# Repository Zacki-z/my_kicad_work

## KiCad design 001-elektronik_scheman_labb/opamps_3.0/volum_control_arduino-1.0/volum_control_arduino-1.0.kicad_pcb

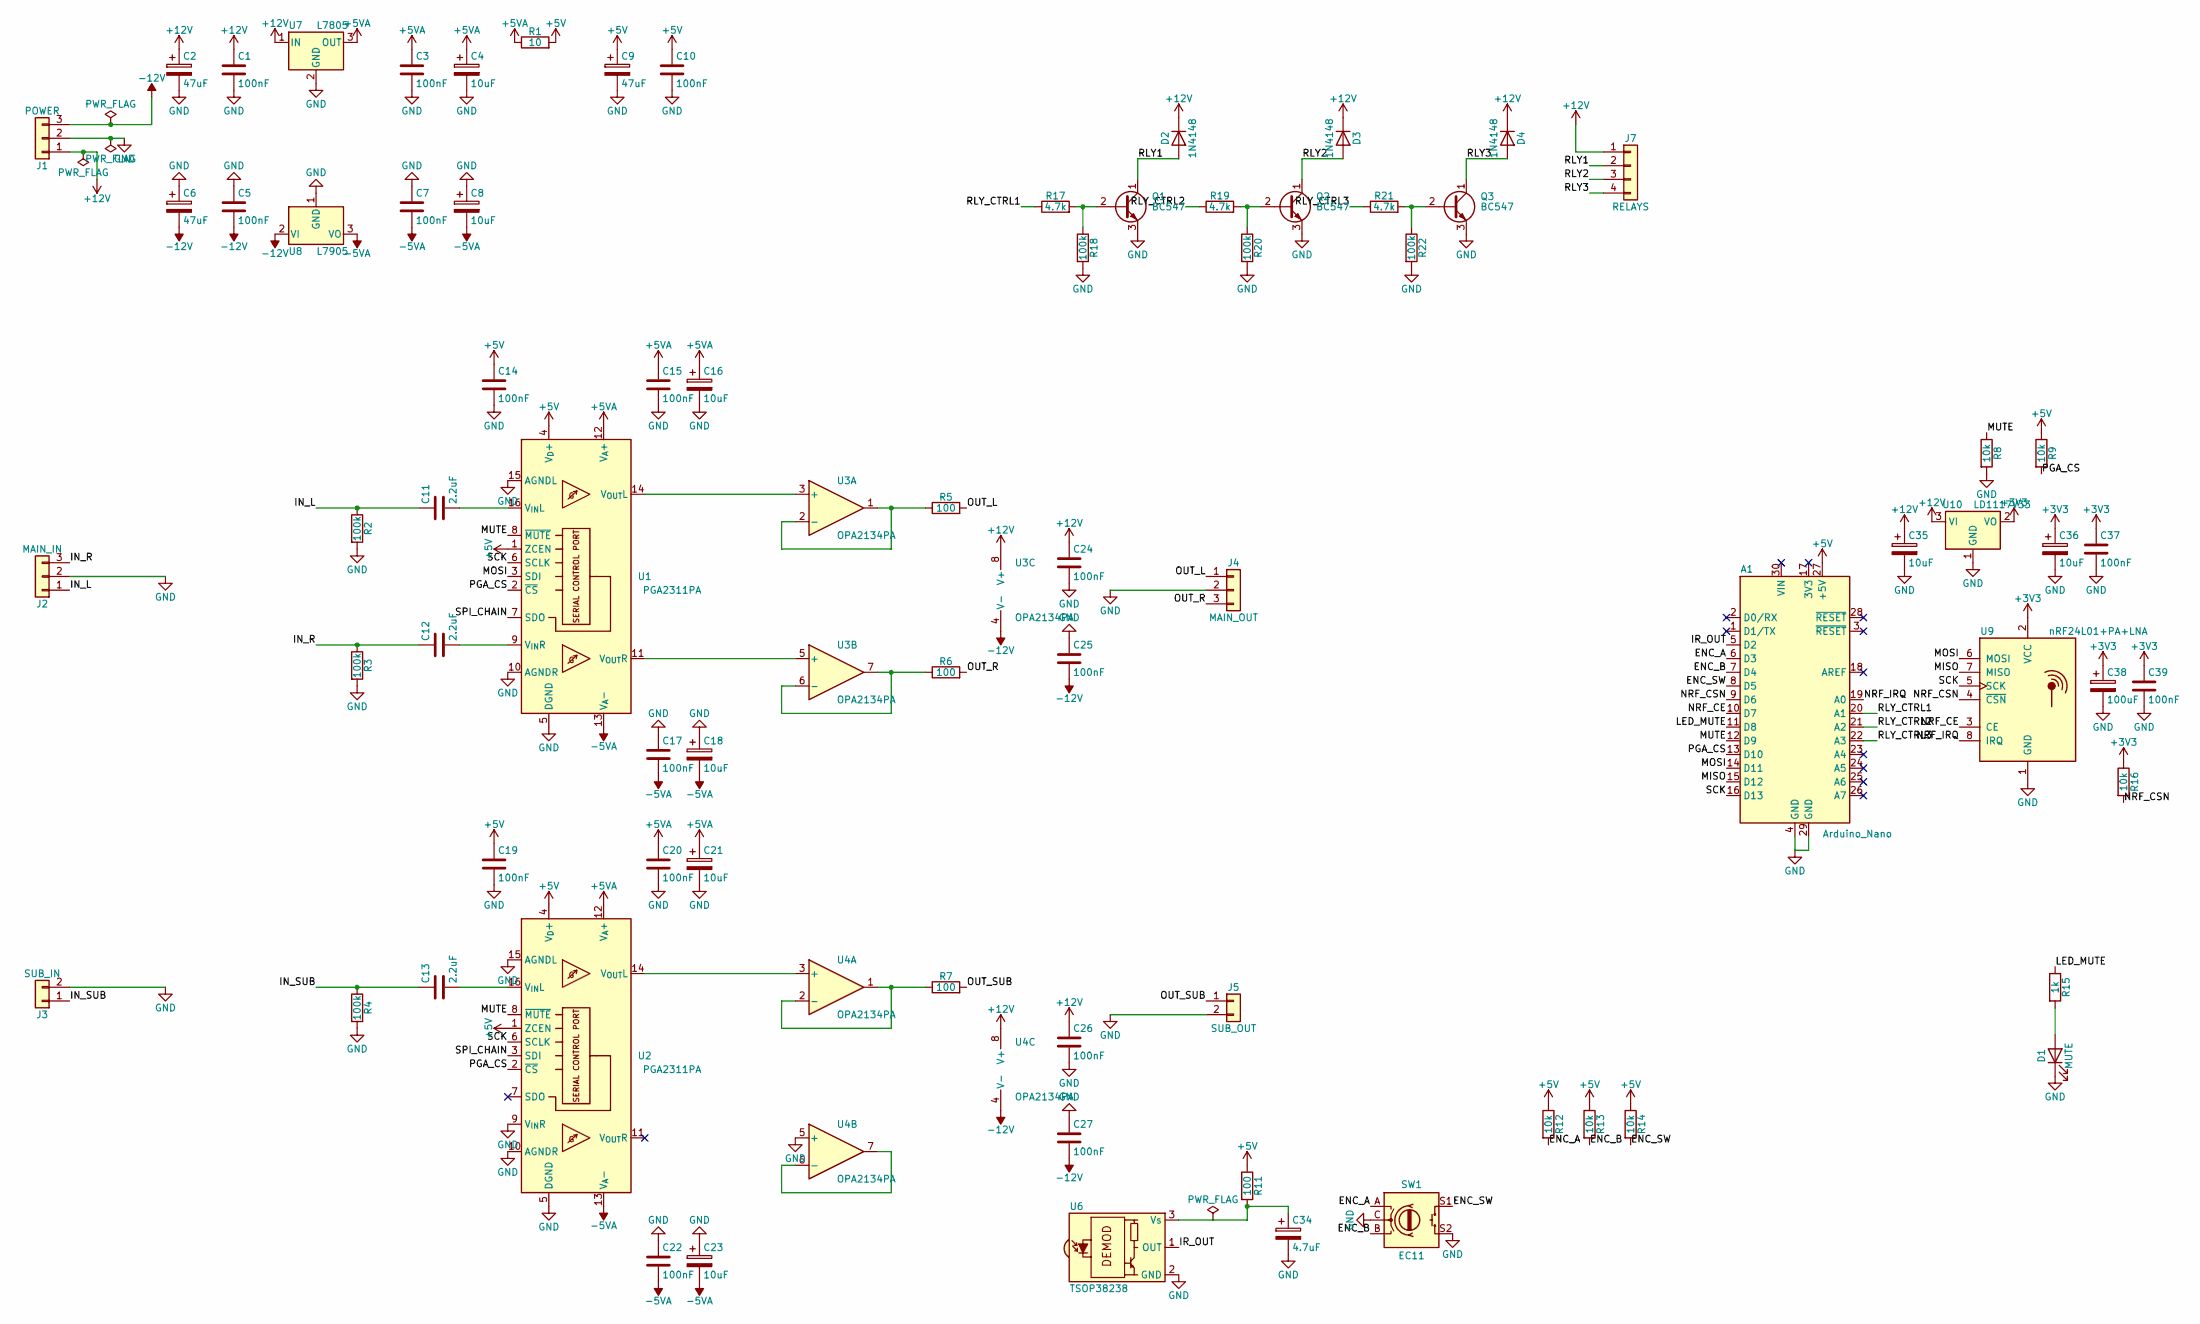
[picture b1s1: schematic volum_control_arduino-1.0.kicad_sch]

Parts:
A1: Arduino_Nano
C1, C3, C5, C7, C10, C14, C15, C17, C19, C20, C22, C24, C25, C26, C27, C37, C39: 100nF; C_Disc_D5.0mm_W2.5mm_P2.50mm
C2, C6, C9: 47uF; CP_Radial_D6.3mm_P2.50mm
C4, C8, C16, C18, C21, C23, C35, C36: 10uF; CP_Radial_D5.0mm_P2.00mm
C11, C12, C13: 2.2uF; C_Rect_L7.2mm_W3.5mm_P5.00mm_FKS2_FKP2_MKS2_MKP2
C34: 4.7uF; CP_Radial_D5.0mm_P2.00mm
C38: 100uF; CP_Radial_D6.3mm_P2.50mm
D1: MUTE; LED_D3.0mm
D2, D3, D4: 1N4148; D_DO-35_SOD27_P7.62mm_Horizontal
J1: POWER; PinHeader_1x03_P2.54mm_Vertical
J2: MAIN_IN; PinHeader_1x03_P2.54mm_Vertical
J3: SUB_IN; PinHeader_1x02_P2.54mm_Vertical
J4: MAIN_OUT; PinHeader_1x03_P2.54mm_Vertical
J5: SUB_OUT; PinHeader_1x02_P2.54mm_Vertical
J7: RELAYS; PinHeader_1x04_P2.54mm_Vertical
Q1, Q2, Q3: BC547; TO-92_Inline
R1: 10; R_Axial_DIN0207_L6.3mm_D2.5mm_P7.62mm_Horizontal
R2, R3, R4, R18, R20, R22: 100k; R_Axial_DIN0207_L6.3mm_D2.5mm_P7.62mm_Horizontal
R5, R6, R7, R11: 100; R_Axial_DIN0207_L6.3mm_D2.5mm_P7.62mm_Horizontal
R8, R9, R12, R13, R14, R16: 10k; R_Axial_DIN0207_L6.3mm_D2.5mm_P7.62mm_Horizontal
R15: 1k; R_Axial_DIN0207_L6.3mm_D2.5mm_P7.62mm_Horizontal
R17, R19, R21: 4.7k; R_Axial_DIN0207_L6.3mm_D2.5mm_P7.62mm_Horizontal
SW1: EC11; RotaryEncoder_Alps_EC11E-Switch_Vertical_H20mm
U1, U2: PGA2311PA; DIP-16_W7.62mm
U3, U4: OPA2134PA; DIP-8_W7.62mm
U6: TSOP38238; Vishay_MINICAST-3Pin
U7: L7805; TO-220-3_Vertical
U8: L7905; TO-220-3_Vertical
U9: nRF24L01+PA+LNA; nRF24L01_Breakout
U10: LD1117V33; TO-220-3_Vertical

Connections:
+3V3: C36.1, C37.1, C38.1, C39.1, R16.1, U9.2 (VCC), U10.2 (VO)
+5V: A1.27 (+5V), C9.1, C10.1, C14.1, C19.1, R1.2, R9.1, R11.1, R12.1, R13.1, R14.1, U1.1 (ZCEN), U1.4 (V_{D}+), U2.1 (ZCEN), U2.4 (V_{D}+)
+5VA: C3.1, C4.1, C15.1, C16.1, C20.1, C21.1, R1.1, U1.12 (V_{A}+), U2.12 (V_{A}+), U7.3 (OUT)
+12V: C1.1, C2.1, C24.1, C26.1, C35.1, D2.1 (K), D3.1 (K), D4.1 (K), J1.1, J7.1, U3.8 (V+), U4.8 (V+), U7.1 (IN), U10.3 (VI)
-5VA: C7.2, C8.2, C17.2, C18.2, C22.2, C23.2, U1.13 (V_{A}-), U2.13 (V_{A}-), U8.3 (VO)
-12V: C5.2, C6.2, C25.2, C27.2, J1.3, U3.4 (V-), U4.4 (V-), U8.2 (VI)
/ENC_A: A1.6 (D3), R12.2, SW1.A
/ENC_B: A1.7 (D4), R13.2, SW1.B
/ENC_SW: A1.8 (D5), R14.2, SW1.S1
/IN_L: C11.1, J2.1, R2.1
/IN_R: C12.1, J2.3, R3.1
/IN_SUB: C13.1, J3.1, R4.1
/IR_OUT: A1.5 (D2), U6.1 (OUT)
/LED_MUTE: A1.11 (D8), R15.1
/MISO: A1.15 (D12), U9.7 (MISO)
/MOSI: A1.14 (D11), U1.3 (SDI), U9.6 (MOSI)
/MUTE: A1.12 (D9), R8.1, U1.8 (~MUTE), U2.8 (~MUTE)
/NRF_CE: A1.10 (D7), U9.3 (CE)
/NRF_CSN: A1.9 (D6), R16.2, U9.4 (~CSN)
/NRF_IRQ: A1.19 (A0), U9.8 (IRQ)
/OUT_L: J4.1, R5.2
/OUT_R: J4.3, R6.2
/OUT_SUB: J5.1, R7.2
/PGA_CS: A1.13 (D10), R9.2, U1.2 (~CS), U2.2 (~CS)
/RLY1: D2.2 (A), J7.2, Q1.1 (C)
/RLY2: D3.2 (A), J7.3, Q2.1 (C)
/RLY3: D4.2 (A), J7.4, Q3.1 (C)
/RLY_CTRL1: A1.20 (A1), R17.1
/RLY_CTRL2: A1.21 (A2), R19.1
/RLY_CTRL3: A1.22 (A3), R21.1
/SCK: A1.16 (D13), U1.6 (SCLK), U2.6 (SCLK), U9.5 (SCK)
/SPI_CHAIN: U1.7 (SDO), U2.3 (SDI)
GND: A1.4 (GND), A1.29 (GND), C1.2, C2.2, C3.2, C4.2, C5.1, C6.1, C7.1, C8.1, C9.2, C10.2, C14.2, C15.2, C16.2, C17.1, C18.1, C19.2, C20.2, C21.2, C22.1, C23.1, C24.2, C25.1, C26.2, C27.1, C34.2, C35.2, C36.2, C37.2, C38.2, C39.2, D1.1 (K), J1.2, J2.2, J3.2, J4.2, J5.2, Q1.3 (E), Q2.3 (E), Q3.3 (E), R2.2, R3.2, R4.2, R8.2, R18.2, R20.2, R22.2, SW1.C, SW1.S2, U1.5 (DGND), U1.10 (AGNDR), U1.15 (AGNDL), U2.5 (DGND), U2.9 (V_{IN}R), U2.10 (AGNDR), U2.15 (AGNDL), U4.5 (+), U6.2 (GND), U7.2 (GND), U8.1 (GND), U9.1 (GND), U10.1 (GND)
unnamed: D1.2 (A), R15.2
unnamed: Q1.2 (B), R17.2, R18.1
unnamed: Q2.2 (B), R19.2, R20.1
unnamed: Q3.2 (B), R21.2, R22.1
unnamed: C11.2, U1.16 (V_{IN}L)
unnamed: C12.2, U1.9 (V_{IN}R)
unnamed: U1.14 (V_{OUT}L), U3.3 (+)
unnamed: U1.11 (V_{OUT}R), U3.5 (+)
unnamed: C13.2, U2.16 (V_{IN}L)
unnamed: U2.14 (V_{OUT}L), U4.3 (+)
unnamed: R5.1, U3.1, U3.2 (-)
unnamed: R6.1, U3.6 (-), U3.7
unnamed: R7.1, U4.1, U4.2 (-)
unnamed: U4.6 (-), U4.7
unnamed: C34.1, R11.2, U6.3 (Vs)

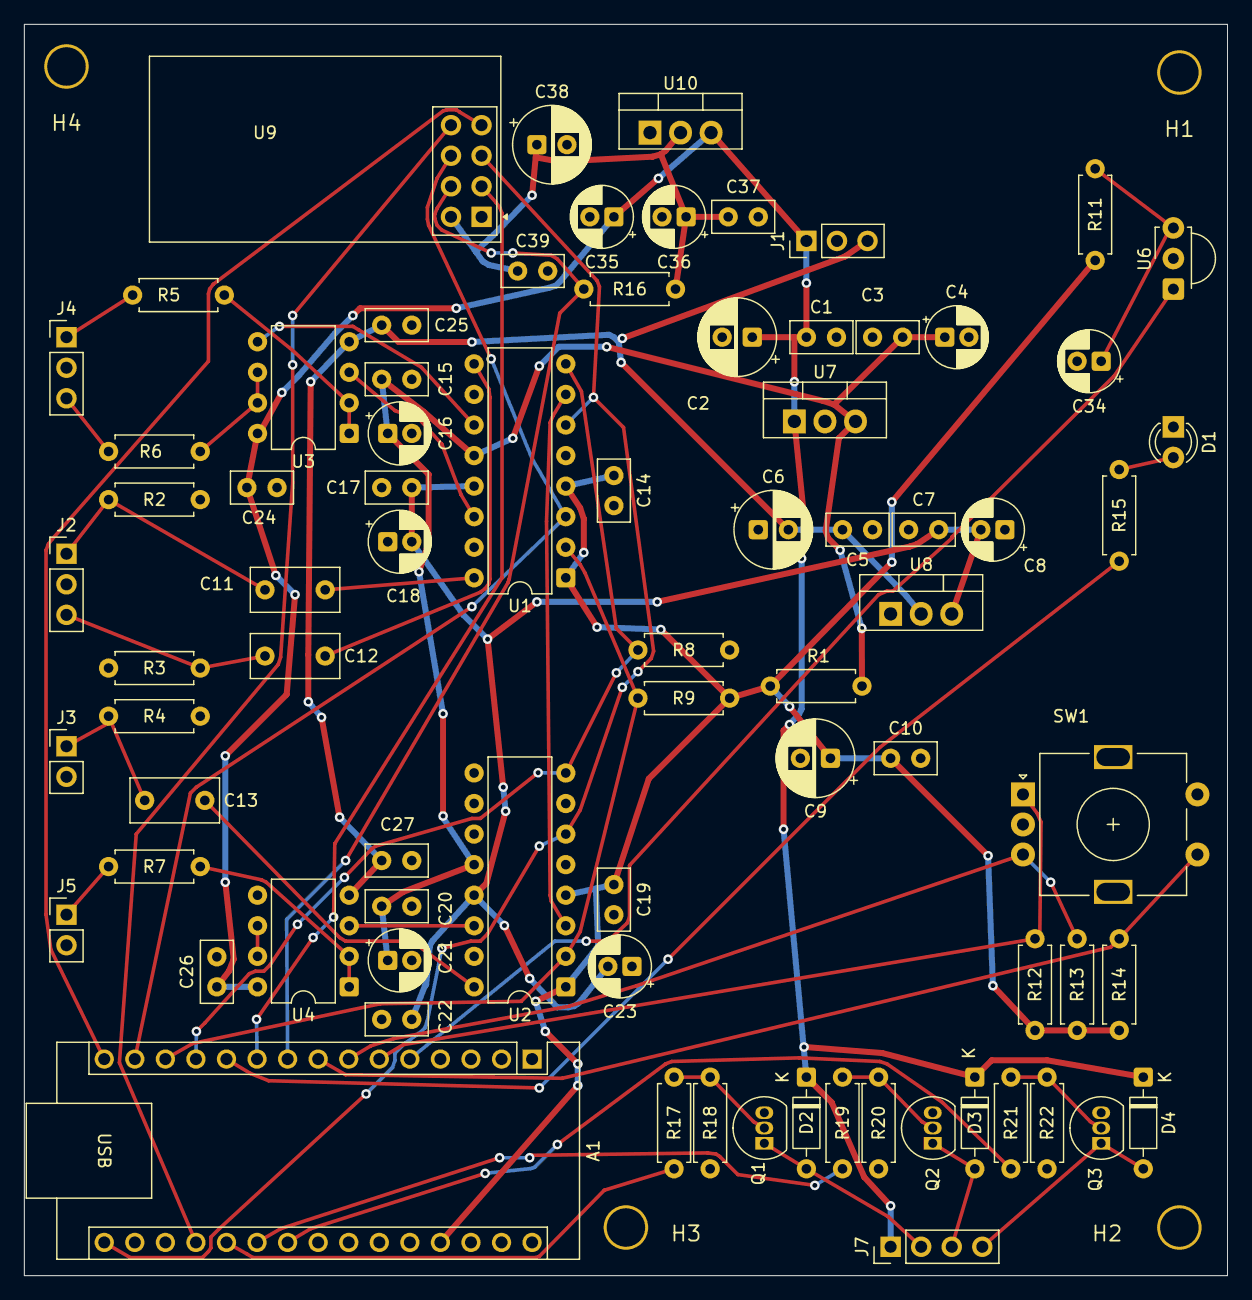
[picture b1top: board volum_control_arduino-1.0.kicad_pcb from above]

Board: 4 copper layers, 100.0 x 104.0 mm, 82 parts (0 on the bottom side), 48 nets.

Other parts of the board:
H1, H2, H3, H4: MountingHole; MountingHole_3.2mm

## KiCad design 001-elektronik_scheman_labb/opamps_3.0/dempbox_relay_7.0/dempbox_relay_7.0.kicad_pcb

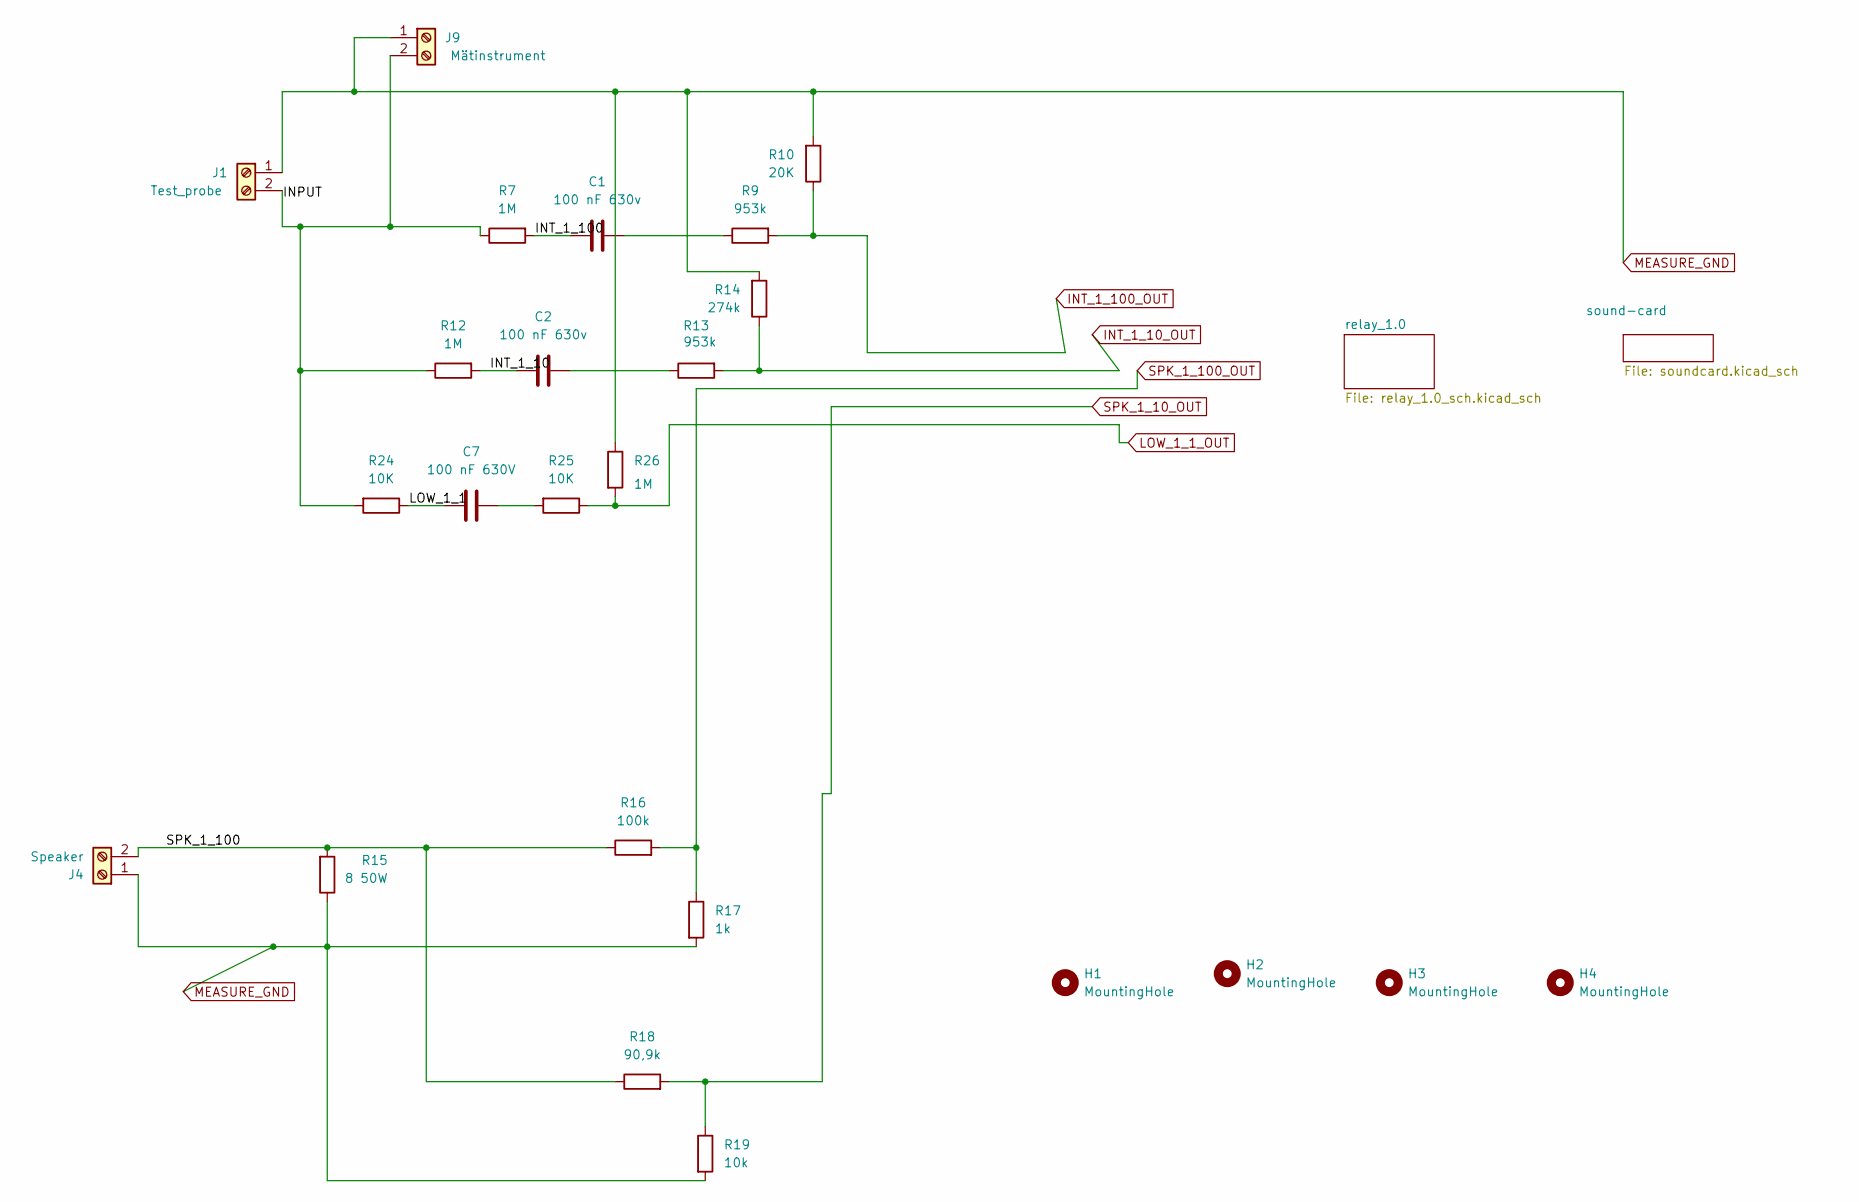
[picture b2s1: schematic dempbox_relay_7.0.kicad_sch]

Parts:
C1, C2: 100 nF 630v; C_Rect_L18.0mm_W6.0mm_P15.00mm_FKS3_FKP3
C7: 100 nF 630V; C_Rect_L18.0mm_W6.0mm_P15.00mm_FKS3_FKP3
H1, H2, H3, H4: MountingHole; MountingHole_3.2mm_M3
J1: Test_probe; TerminalBlock_Phoenix_MKDS-1,5-2-5.08_1x02_P5.08mm_Horizont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
J4: Speaker; PinSocket_1x02_P2.54mm_Vertical
J9: Mätinstrument; TerminalBlock_Phoenix_MKDS-1,5-2-5.08_1x02_P5.08mm_Horizont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
R7, R12, R26: 1M; R_Axial_DIN0204_L3.6mm_D1.6mm_P7.62mm_Horizontal
R9, R13: 953k; R_Axial_DIN0204_L3.6mm_D1.6mm_P7.62mm_Horizontal
R10: 20K; R_Axial_DIN0204_L3.6mm_D1.6mm_P7.62mm_Horizontal
R14: 274k; R_Axial_DIN0204_L3.6mm_D1.6mm_P7.62mm_Horizontal
R15: 8 50W; PinSocket_1x02_P2.54mm_Vertical
R16: 100k; R_Axial_DIN0204_L3.6mm_D1.6mm_P7.62mm_Horizontal
R17: 1k; R_Axial_DIN0204_L3.6mm_D1.6mm_P7.62mm_Horizontal
R18: 90,9k; R_Axial_DIN0204_L3.6mm_D1.6mm_P7.62mm_Horizontal
R19: 10k; R_Axial_DIN0204_L3.6mm_D1.6mm_P7.62mm_Horizontal
R24, R25: 10K; R_Axial_DIN0204_L3.6mm_D1.6mm_P7.62mm_Horizontal

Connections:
/INPUT: J1.2, J9.2, R7.1, R12.1, R24.2
/INT_1_10: C2.1, R12.2
/INT_1_100: C1.1, R7.2
/LOW_1_1: C7.2, R24.1
/SPK_1_100: J4.2, R15.2, R16.1, R18.1
INT_1_10_OUT: R13.2, R14.1; also elsewhere on the board
INT_1_100_OUT: R9.2, R10.1; also elsewhere on the board
LOW_1_1_OUT: R25.1, R26.2; also elsewhere on the board
MEASURE_GND: J1.1, J4.1, J9.1, R10.2, R14.2, R15.1, R17.2, R19.2, R26.1; also elsewhere on the board
unnamed: C1.2, R9.1
unnamed: C2.2, R13.1
unnamed: C7.1, R25.2
SPK_1_10_OUT: R18.2, R19.1; also elsewhere on the board
SPK_1_100_OUT: R16.2, R17.1; also elsewhere on the board

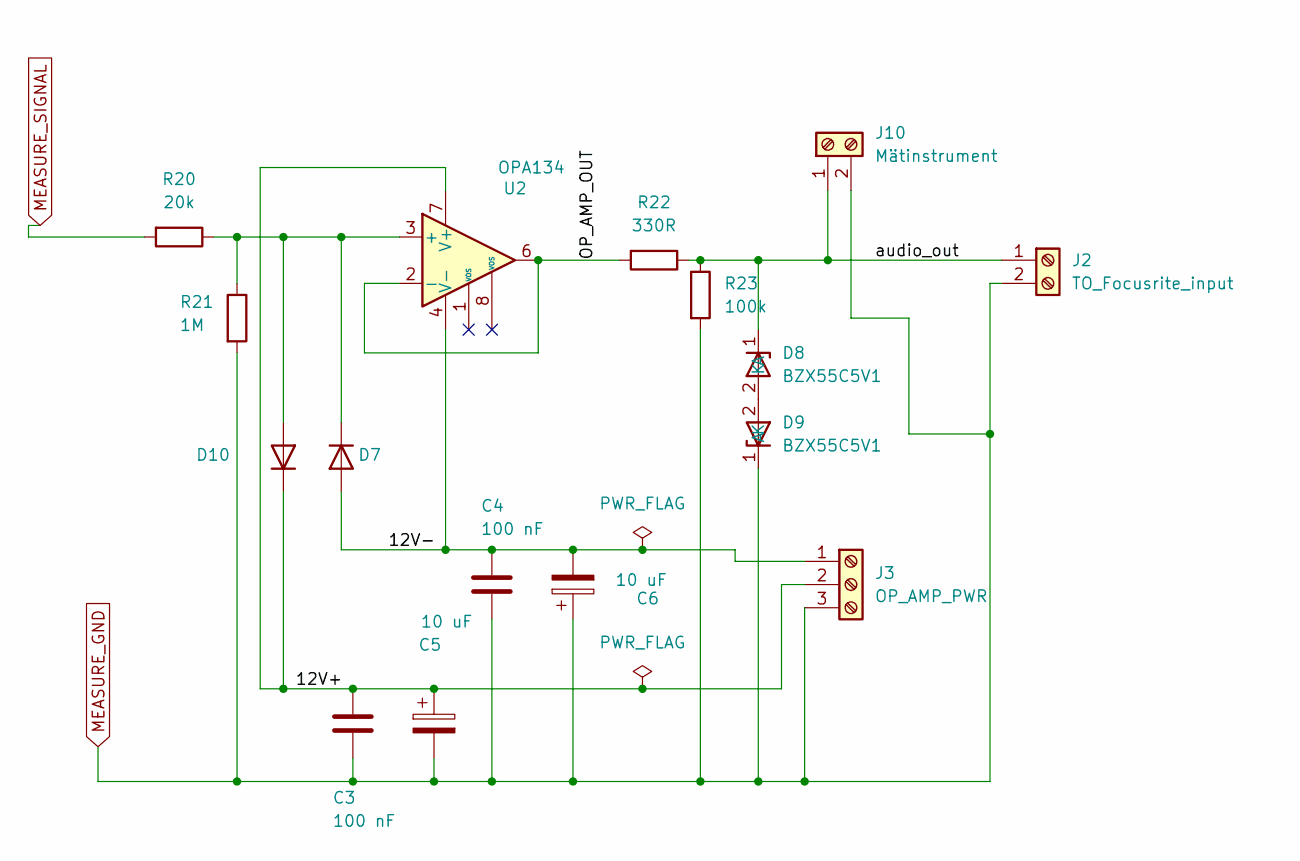
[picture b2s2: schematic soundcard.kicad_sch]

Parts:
C3, C4: 100 nF; C_Disc_D3.4mm_W2.1mm_P2.50mm
C5, C6: 10 uF; CP_Radial_D5.0mm_P2.50mm
D7, D10: 1N4148; D_DO-35_SOD27_P7.62mm_Horizontal
D8, D9: BZX55C5V1; D_DO-35_SOD27_P7.62mm_Horizontal
J2: TO_Focusrite_input; PinSocket_1x02_P2.54mm_Vertical
J3: OP_AMP_PWR; PinSocket_1x03_P2.54mm_Vertical
J10: Mätinstrument; PinSocket_1x02_P2.54mm_Vertical
R20: 20k; R_Axial_DIN0204_L3.6mm_D1.6mm_P7.62mm_Horizontal
R21: 1M; R_Axial_DIN0204_L3.6mm_D1.6mm_P7.62mm_Horizontal
R22: 330R; R_Axial_DIN0204_L3.6mm_D1.6mm_P7.62mm_Horizontal
R23: 100k; R_Axial_DIN0204_L3.6mm_D1.6mm_P7.62mm_Horizontal
U2: OPA134; CERDIP-8_W7.62mm_SideBrazed_Socket

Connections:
/sound-card/12V+: C3.1, C5.1, D10.1 (K), J3.2, U2.7 (V+)
/sound-card/12V-: C4.1, C6.2, D7.2 (A), J3.1, U2.4 (V-)
/sound-card/OP_AMP_OUT: R22.2, U2.2 (-), U2.6
/sound-card/audio_out: D8.1 (K), J2.1, J10.1, R22.1, R23.1
MEASURE_GND: C3.2, C4.2, C5.2, C6.1, D9.1 (K), J2.2, J3.3, J10.2, R21.2, R23.2; also elsewhere on the board
MEASURE_SIGNAL: R20.2; also elsewhere on the board
unnamed: D8.2 (A), D9.2 (A)
unnamed: D7.1 (K), D10.2 (A), R20.1, R21.1, U2.3 (+)

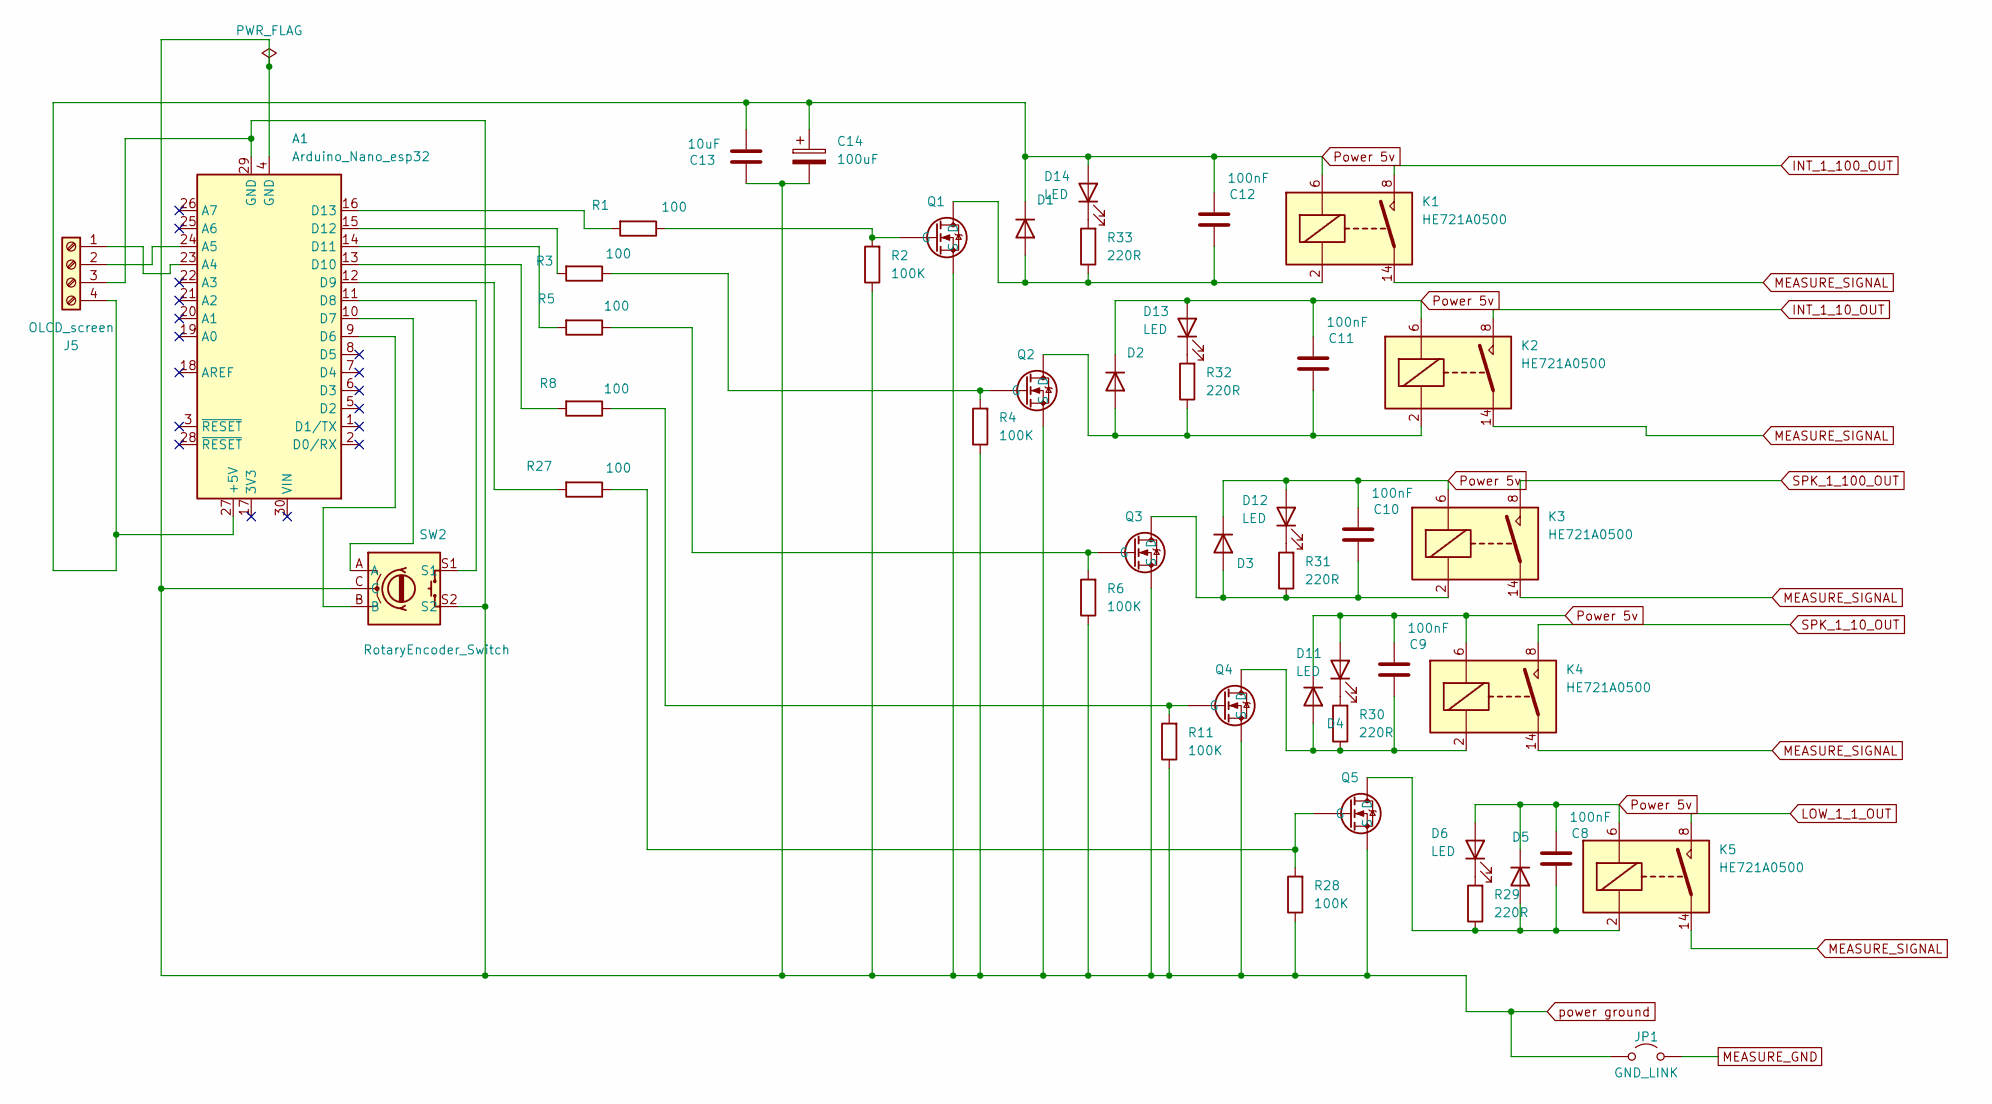
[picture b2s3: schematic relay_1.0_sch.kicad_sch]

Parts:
A1: Arduino_Nano_esp32; Arduino_Nano
C8, C9, C10, C11, C12: 100nF; C_Disc_D3.4mm_W2.1mm_P2.50mm
C13: 10uF; C_Disc_D5.0mm_W2.5mm_P5.00mm
C14: 100uF; CP_Radial_D6.3mm_P2.50mm
D1, D2, D3, D4, D5: 1N4003; D_DO-41_SOD81_P10.16mm_Horizontal
D6, D11, D12, D13, D14: LED; LED_D3.0mm
J5: OLCD_screen; PinSocket_1x04_P2.54mm_Vertical
JP1: GND_LINK; PinHeader_1x02_P2.54mm_Vertical
K1, K2, K3, K4, K5: HE721A0500; Relay_StandexMeder_DIP_LowProfile
Q1, Q2, Q3, Q4, Q5: 2N7000; TO-92_Inline
R1, R3, R5, R8, R27: 100; R_Axial_DIN0204_L3.6mm_D1.6mm_P7.62mm_Horizontal
R2, R4, R6, R11, R28: 100K; R_Axial_DIN0204_L3.6mm_D1.6mm_P7.62mm_Horizontal
R29, R30, R31, R32, R33: 220R; R_Axial_DIN0204_L3.6mm_D1.6mm_P7.62mm_Horizontal
SW2: RotaryEncoder_Switch; RotaryEncoder_Alps_EC11E-Switch_Vertical_H20mm

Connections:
INT_1_10_OUT: K2.8; also elsewhere on the board
INT_1_100_OUT: K1.8; also elsewhere on the board
LOW_1_1_OUT: K5.8; also elsewhere on the board
MEASURE_GND: JP1.2 (B); also elsewhere on the board
MEASURE_SIGNAL: K1.14, K2.14, K3.14, K4.14, K5.14; also elsewhere on the board
unnamed: A1.23 (A4), J5.1
unnamed: A1.24 (A5), J5.2
unnamed: A1.9 (D6), SW2.B
unnamed: A1.10 (D7), SW2.A
unnamed: A1.11 (D8), SW2.S1
unnamed: A1.12 (D9), R27.2
unnamed: A1.13 (D10), R8.2
unnamed: A1.14 (D11), R5.2
unnamed: A1.15 (D12), R3.2
unnamed: A1.16 (D13), R1.2
unnamed: C12.2, D1.2 (A), K1.2, Q1.3 (D), R33.1
unnamed: C11.2, D2.2 (A), K2.2, Q2.3 (D), R32.1
unnamed: C10.2, D3.2 (A), K3.2, Q3.3 (D), R31.1
unnamed: C9.2, D4.2 (A), K4.2, Q4.3 (D), R30.1
unnamed: C8.2, D5.2 (A), K5.2, Q5.3 (D), R29.1
unnamed: D6.1 (K), R29.2
unnamed: D11.1 (K), R30.2
unnamed: D12.1 (K), R31.2
unnamed: D13.1 (K), R32.2
unnamed: D14.1 (K), R33.2
unnamed: Q1.2 (G), R1.1, R2.2
unnamed: Q2.2 (G), R3.1, R4.2
unnamed: Q3.2 (G), R5.1, R6.2
unnamed: Q4.2 (G), R8.1, R11.2
unnamed: Q5.2 (G), R27.1, R28.2
Power 5v: A1.27 (+5V), C8.1, C9.1, C10.1, C11.1, C12.1, C13.1, C14.1, D1.1 (K), D2.1 (K), D3.1 (K), D4.1 (K), D5.1 (K), D6.2 (A), D11.2 (A), D12.2 (A), D13.2 (A), D14.2 (A), J5.4, K1.6, K2.6, K3.6, K4.6, K5.6
SPK_1_10_OUT: K4.8; also elsewhere on the board
SPK_1_100_OUT: K3.8; also elsewhere on the board
power ground: A1.4 (GND), A1.29 (GND), C13.2, C14.2, J5.3, JP1.1 (A), Q1.1 (S), Q2.1 (S), Q3.1 (S), Q4.1 (S), Q5.1 (S), R2.1, R4.1, R6.1, R11.1, R28.1, SW2.C, SW2.S2

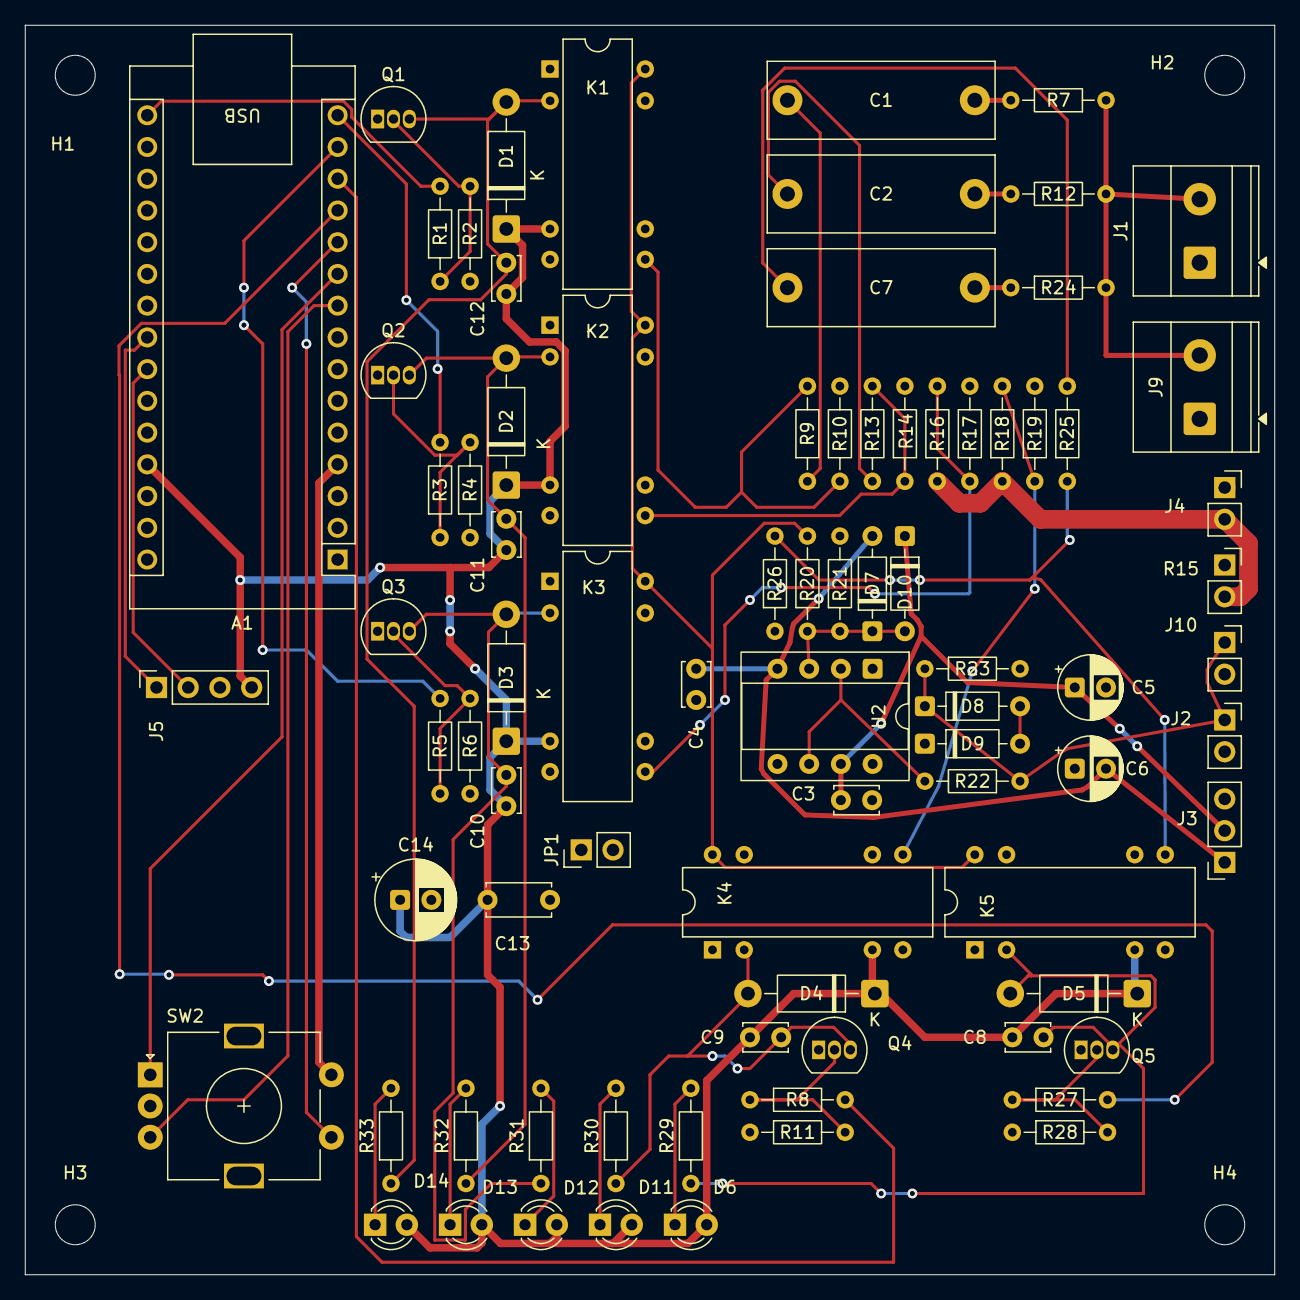
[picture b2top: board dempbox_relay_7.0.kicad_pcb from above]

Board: 2 copper layers, 100.0 x 100.0 mm, 86 parts (0 on the bottom side), 48 nets.

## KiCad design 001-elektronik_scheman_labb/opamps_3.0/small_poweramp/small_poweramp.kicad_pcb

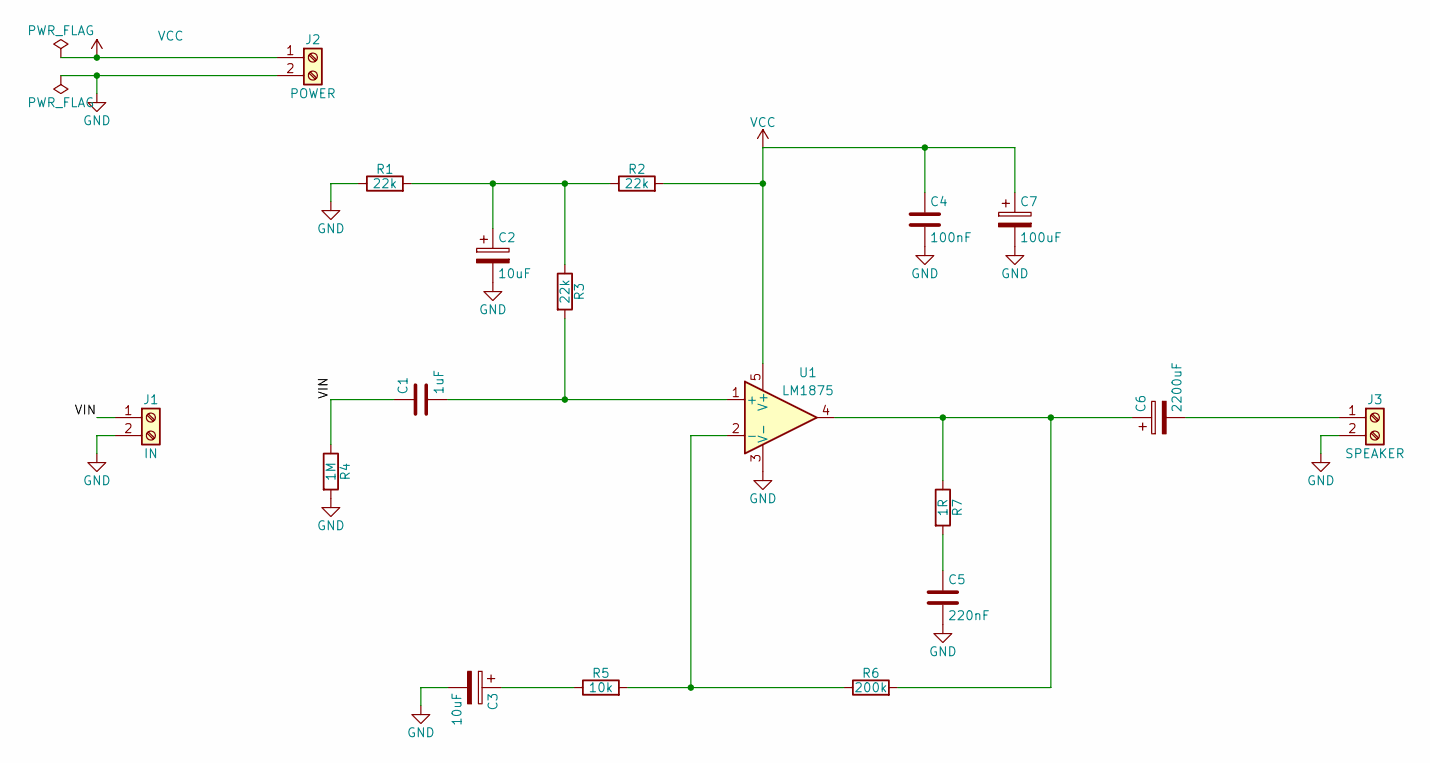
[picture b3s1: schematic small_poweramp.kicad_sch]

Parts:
C1: 1uF; C_Rect_L7.2mm_W3.5mm_P5.00mm_FKS2_FKP2_MKS2_MKP2
C2, C3: 10uF; CP_Radial_D5.0mm_P2.50mm
C4: 100nF; C_Disc_D5.0mm_W2.5mm_P5.00mm
C5: 220nF; C_Rect_L7.2mm_W3.5mm_P5.00mm_FKS2_FKP2_MKS2_MKP2
C6: 2200uF; CP_Radial_D16.0mm_P7.50mm
C7: 100uF; CP_Radial_D8.0mm_P3.50mm
J1: IN; TerminalBlock_Phoenix_MKDS-1,5-2-5.08_1x02_P5.08mm_Horizont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
J2: POWER; TerminalBlock_Phoenix_MKDS-1,5-2-5.08_1x02_P5.08mm_Horizont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
J3: SPEAKER; TerminalBlock_Phoenix_MKDS-1,5-2-5.08_1x02_P5.08mm_Horizont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
R1, R2, R3: 22k; R_Axial_DIN0207_L6.3mm_D2.5mm_P10.16mm_Horizontal
R4: 1M; R_Axial_DIN0207_L6.3mm_D2.5mm_P10.16mm_Horizontal
R5: 10k; R_Axial_DIN0207_L6.3mm_D2.5mm_P10.16mm_Horizontal
R6: 200k; R_Axial_DIN0207_L6.3mm_D2.5mm_P10.16mm_Horizontal
R7: 1R; R_Axial_DIN0207_L6.3mm_D2.5mm_P10.16mm_Horizontal
U1: LM1875; TO-220-5_P3.4x3.7mm_StaggerOdd_Lead3.8mm_Vertical

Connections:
/VIN: C1.1, J1.1, R4.1
GND: C2.2, C3.2, C4.2, C5.2, C7.2, J1.2, J2.2, J3.2, R1.1, R4.2, U1.3 (V-)
unnamed: C2.1, R1.2, R2.1, R3.1
unnamed: C3.1, R5.1
unnamed: C5.1, R7.2
unnamed: C6.1, R6.2, R7.1, U1.4
unnamed: C6.2, J3.1
unnamed: C1.2, R3.2, U1.1 (+)
unnamed: R5.2, R6.1, U1.2 (-)
VCC: C4.1, C7.1, J2.1, R2.2, U1.5 (V+)

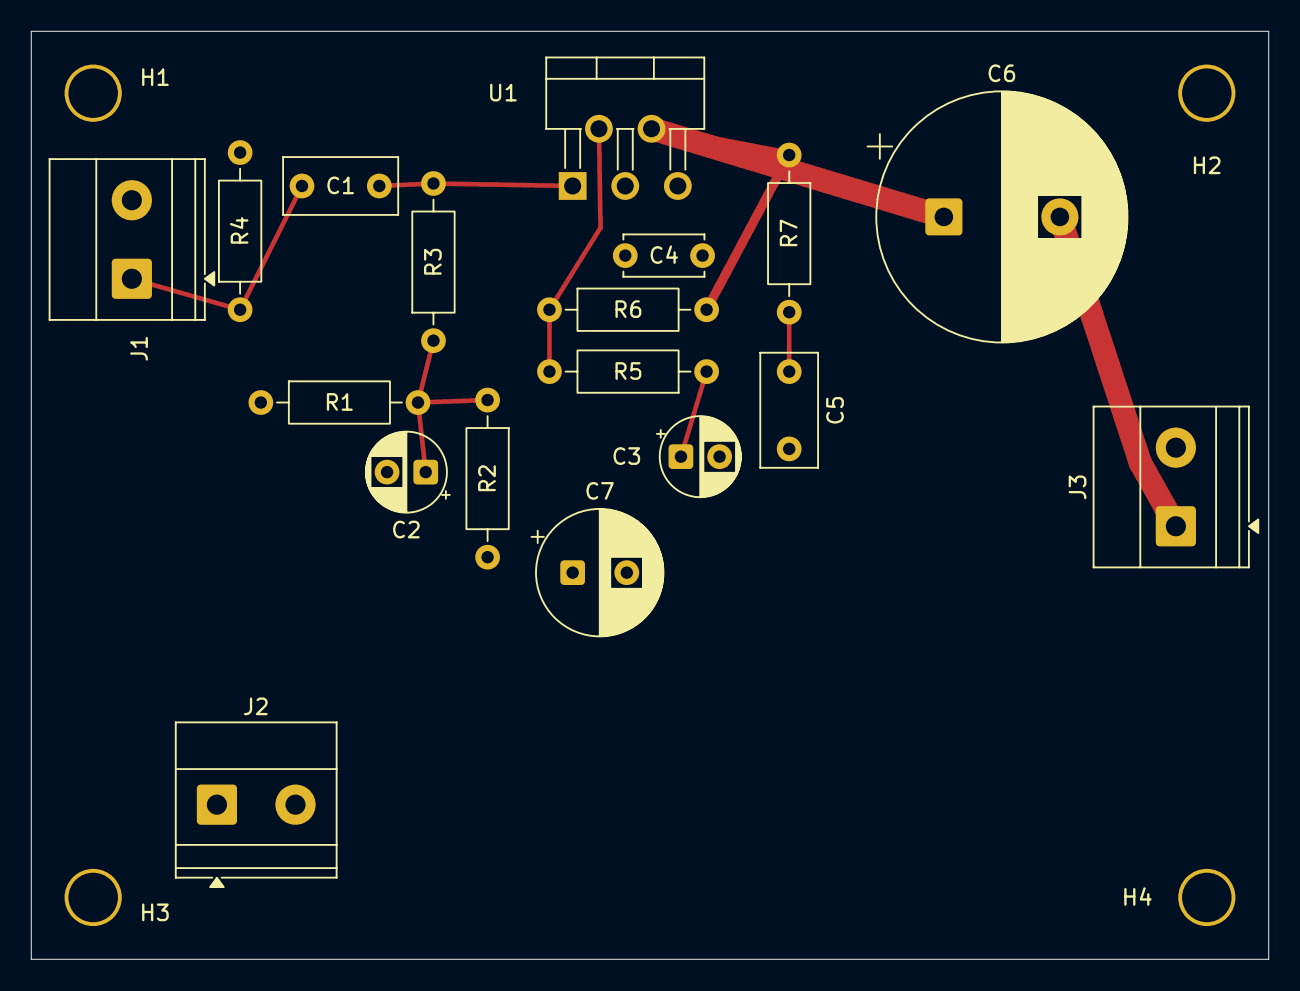
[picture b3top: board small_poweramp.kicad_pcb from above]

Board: 4 copper layers, 80.0 x 60.0 mm, 22 parts (0 on the bottom side), 10 nets.

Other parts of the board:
H1, H2, H3, H4: MountingHole; MountingHole_3.2mm
